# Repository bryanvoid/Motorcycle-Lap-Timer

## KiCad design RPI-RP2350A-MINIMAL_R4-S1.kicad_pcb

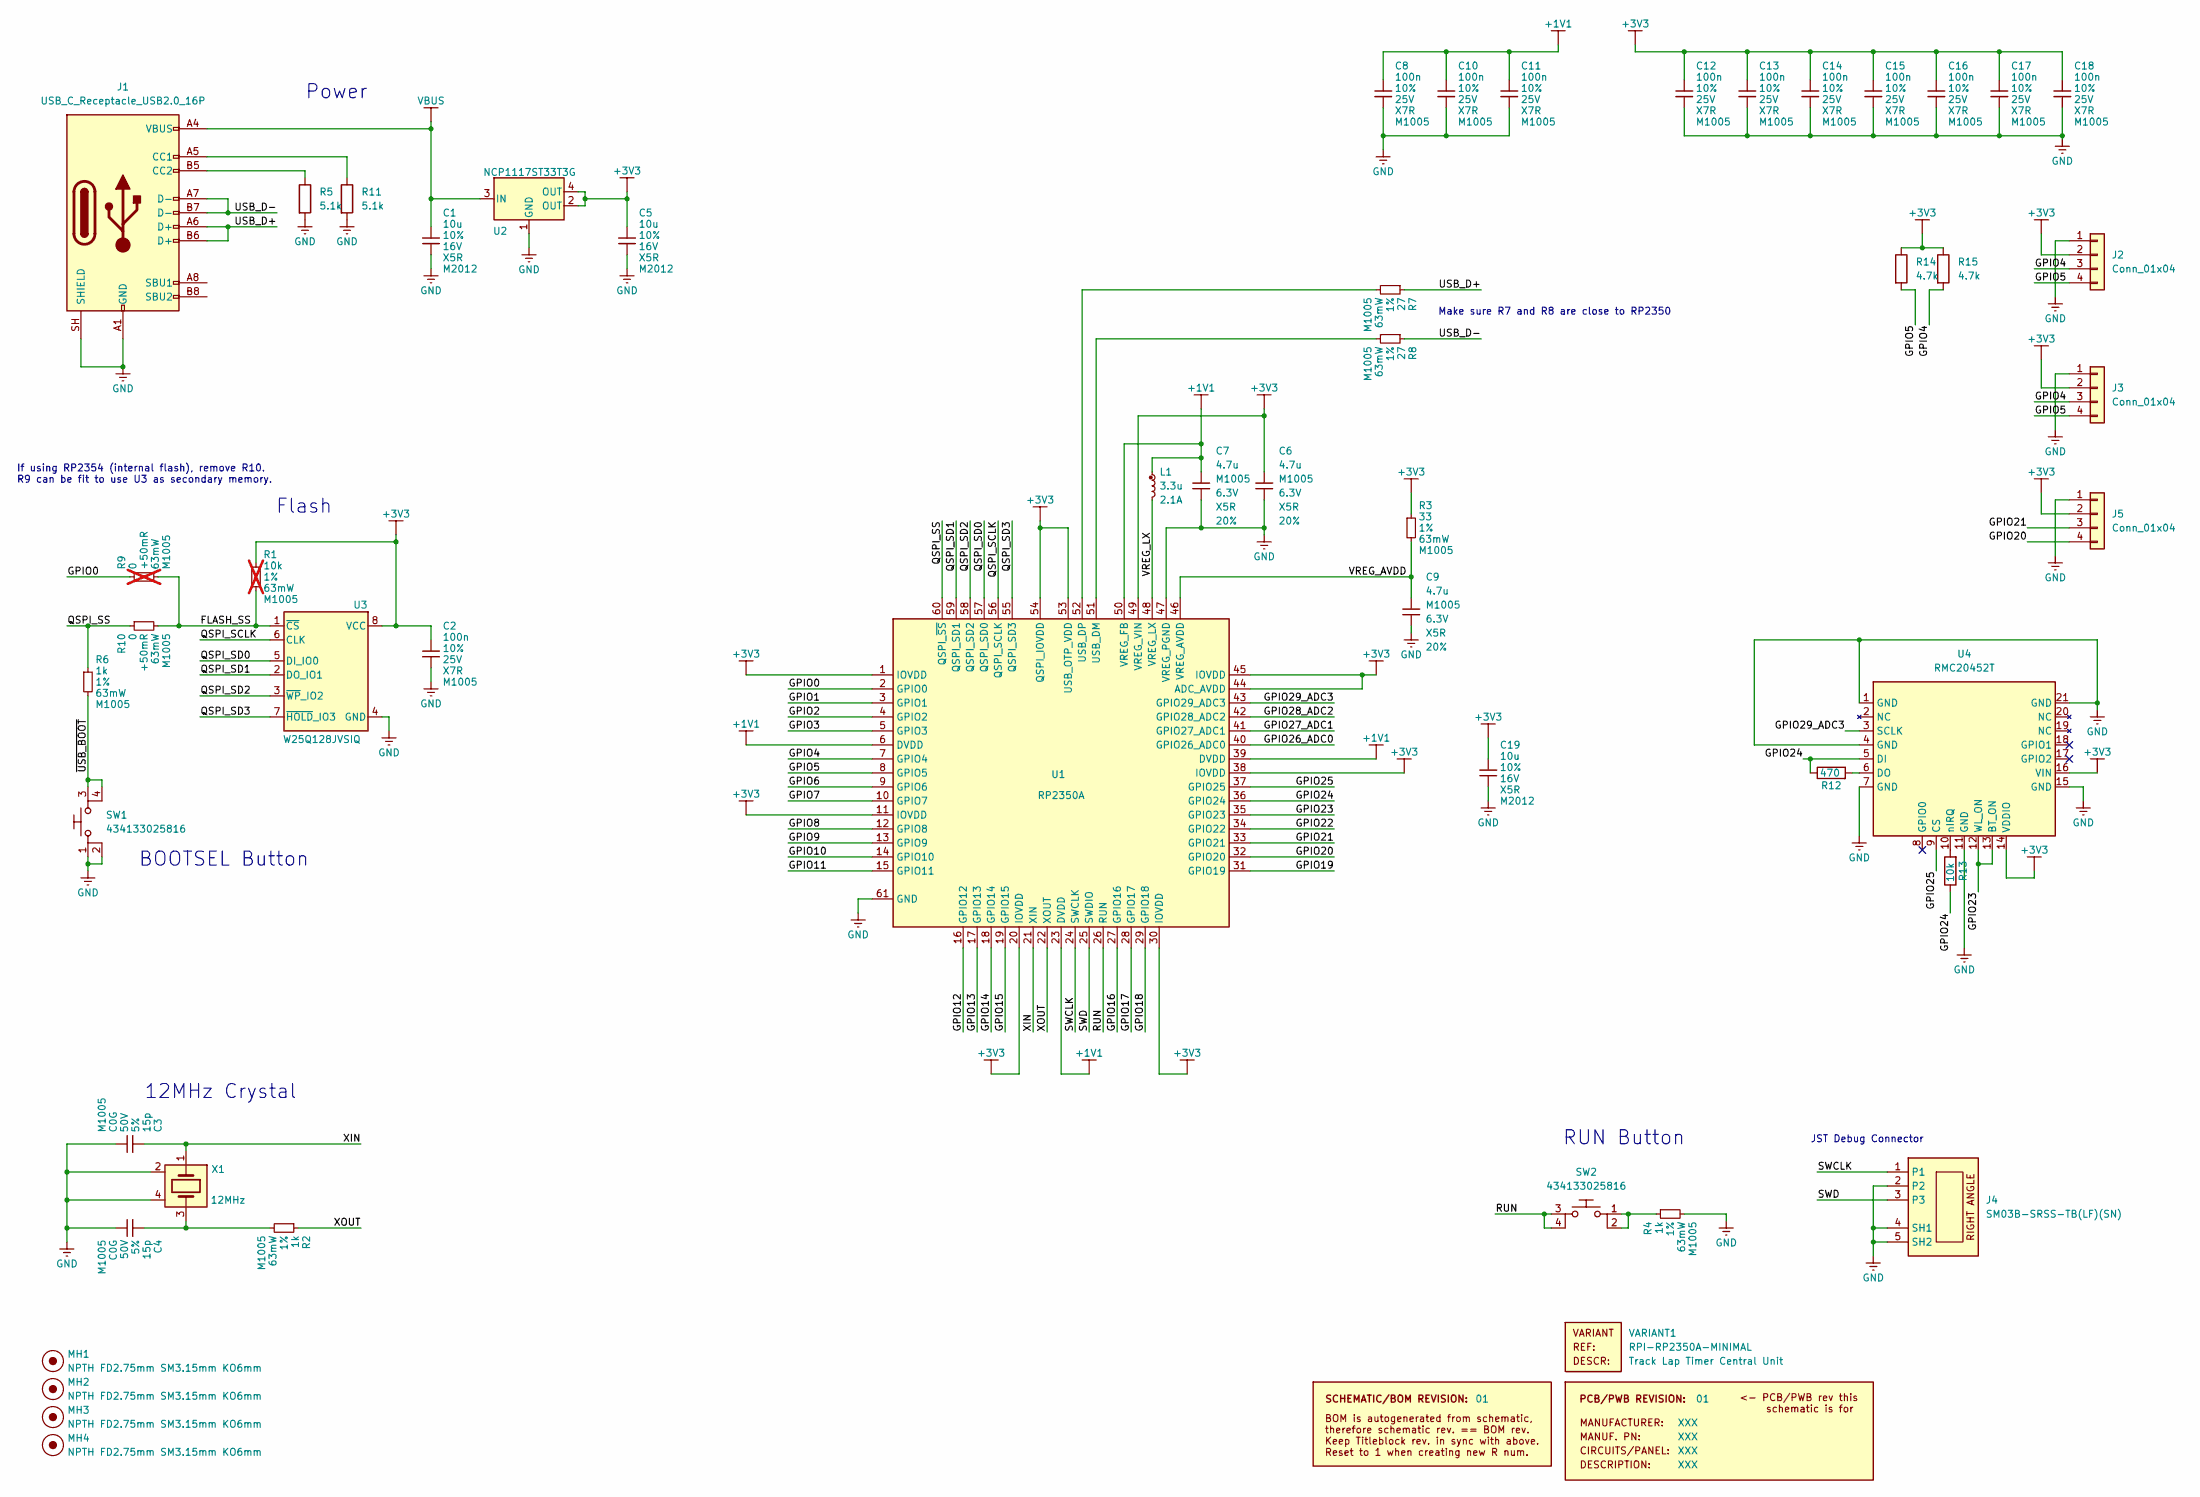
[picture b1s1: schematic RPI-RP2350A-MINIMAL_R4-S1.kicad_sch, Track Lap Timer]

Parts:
C1, C5, C19: 10u; generic_capc2012x125; voltage 16V; tolerance 10%; part_uid RP-01GYSK-AVBE41; LCSC C1035
C2, C8, C10, C11, C12, C13, C14, C15, C16, C17, C18: 100n; generic_capc1005x50; voltage 25V; tolerance 10%; part_uid RP-01BJ9Y-KRGF41; LCSC C1525
C3, C4: 15p; generic_capc1005x50; voltage 50V; tolerance 5%; part_uid RP-01C89W-LLY9XV; LCSC C1548
C6, C7: 4.7u; generic_capc1005x50_wide; voltage 6.3V; tolerance 20%; part_uid RP-019A1P-0C2GHY; LCSC C23733
C9: 4.7u; generic_capc1005x50; voltage 6.3V; tolerance 20%; part_uid RP-019A1P-0C2GHY; LCSC C23733
J1: USB_C_Receptacle_USB2.0_16P; USB_C_Receptacle_GCT_USB4110; LCSC C5143397
J2, J3, J5: Conn_01x04; JST_SH_SM04B-SRSS-TB_1x04-1MP_P1.00mm_Horizontal
J4: SM03B-SRSS-TB(LF)(SN); jst_sm03b-srss-tb-lf--sn-; part_uid RP-01EKJ1-8V9SV1; LCSC C160403
L1: 3.3u; L_Cenker_CKCS201610; tolerance 20%; part_uid RP-01GY5D-2VC7WP; LCSC C98035
MH1, MH2, MH3, MH4: NPTH FD2.75mm SM3.15mm KO6mm; none_mh_npth_fd2p75mm_sm3p15mm_ko6mm; part_uid RP-01HF5R-LCTEJS
PCB1: 01; manufacturer_pn XXX
R1: 10k; generic_resc1005x35; tolerance 1%; voltage 50V; part_uid RP-019A1P-53DHSX; LCSC C11616; not fitted
R2, R4, R6: 1k; generic_resc1005x35; tolerance 1%; voltage 50V; part_uid RP-019A1P-4Z6ZWY; LCSC C11702
R3: 33; generic_resc1005x35; tolerance 1%; voltage 50V; part_uid RP-019A1P-58PW9L; LCSC C25105
R5, R11: 5.1k; R_0402_1005Metric; LCSC C25905
R7, R8: 27; generic_resc1005x35; tolerance 1%; voltage 50V; part_uid RP-01C89V-LTEYC4; LCSC C25156
R9: 0; generic_resc1005x35; tolerance +50mR; voltage 50V; part_uid RP-019A1P-4Y4V63; LCSC C1002; not fitted
R10: 0; generic_resc1005x35; tolerance +50mR; voltage 50V; part_uid RP-019A1P-4Y4V63; LCSC C1002
R12: 470; R_0402_1005Metric; LCSC C25117
R13: 10k; R_0402_1005Metric; LCSC C25744
R14, R15: 4.7k; R_0402_1005Metric
SBREV1: 01
SW1, SW2: 434133025816; wurthelek_434133025816; part_uid RP-01H0MT-6E9H8F; LCSC C5504987
U1: RP2350A; rpi_rp2350a_vias; part_uid RP-01HA9H-9K5E8T; LCSC C42411118
U2: NCP1117ST33T3G; onsemi_ncp1117st33t3g; voltage 3.3V; part_uid RP-01JWD9-7JRX6J; LCSC C26537
U3: W25Q128JVSIQ; generic_soic127p790x195-8; voltage 2.7-3.6V; part_uid RP-01JWD4-F1H4N9; LCSC C97521
U4: RMC20452T; LCSC C49451547
VARIANT1: RPI-RP2350A-MINIMAL
X1: 12MHz; ABM8-272-T3_ABR; tolerance 30ppm; part_uid RP-01G8X7-GS352B; LCSC C9002

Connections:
+1V1: C7.1, C8.1, C10.1, C11.1, L1.1, U1.6 (DVDD), U1.23 (DVDD), U1.39 (DVDD), U1.50 (VREG_FB)
+3V3: C2.1, C5.1, C6.1, C12.1, C13.1, C14.1, C15.1, C16.1, C17.1, C18.1, C19.1, J2.2, J3.2, J5.2, R1.1, R3.1, R14.1, R15.1, U1.1 (IOVDD), U1.11 (IOVDD), U1.20 (IOVDD), U1.30 (IOVDD), U1.38 (IOVDD), U1.44 (ADC_AVDD), U1.45 (IOVDD), U1.49 (VREG_VIN), U1.53 (USB_OTP_VDD), U1.54 (QSPI_IOVDD), U2.2 (OUT), U2.4 (OUT), U3.8 (VCC), U4.14 (VDDIO), U4.16 (VIN)
/FLASH_SS: R1.2, R9.2, R10.2, U3.1 (~CS)
/GPIO0: R9.1, U1.2 (GPIO0)
/GPIO1: U1.3 (GPIO1)
/GPIO2: U1.4 (GPIO2)
/GPIO3: U1.5 (GPIO3)
/GPIO4: J2.3, J3.3, R15.2, U1.7 (GPIO4)
/GPIO5: J2.4, J3.4, R14.2, U1.8 (GPIO5)
/GPIO6: U1.9 (GPIO6)
/GPIO7: U1.10 (GPIO7)
/GPIO8: U1.12 (GPIO8)
/GPIO9: U1.13 (GPIO9)
/GPIO10: U1.14 (GPIO10)
/GPIO11: U1.15 (GPIO11)
/GPIO12: U1.16 (GPIO12)
/GPIO13: U1.17 (GPIO13)
/GPIO14: U1.18 (GPIO14)
/GPIO15: U1.19 (GPIO15)
/GPIO16: U1.27 (GPIO16)
/GPIO17: U1.28 (GPIO17)
/GPIO18: U1.29 (GPIO18)
/GPIO19: U1.31 (GPIO19)
/GPIO20: J5.4, U1.32 (GPIO20)
/GPIO21: J5.3, U1.33 (GPIO21)
/GPIO22: U1.34 (GPIO22)
/GPIO23: U1.35 (GPIO23), U4.12 (WL_ON), U4.13 (BT_ON)
/GPIO24: R12.1, R13.1, U1.36 (GPIO24), U4.5 (DI)
/GPIO25: U1.37 (GPIO25), U4.9 (CS)
/GPIO26_ADC0: U1.40 (GPIO26_ADC0)
/GPIO27_ADC1: U1.41 (GPIO27_ADC1)
/GPIO28_ADC2: U1.42 (GPIO28_ADC2)
/GPIO29_ADC3: U1.43 (GPIO29_ADC3), U4.3 (SCLK)
/QSPI_SCLK: U1.56 (QSPI_SCLK), U3.6 (CLK)
/QSPI_SD0: U1.57 (QSPI_SD0), U3.5 (DI_IO0)
/QSPI_SD1: U1.59 (QSPI_SD1), U3.2 (DO_IO1)
/QSPI_SD2: U1.58 (QSPI_SD2), U3.3 (~WP_IO2)
/QSPI_SD3: U1.55 (QSPI_SD3), U3.7 (~HOLD_IO3)
/QSPI_SS: R6.1, R10.1, U1.60 (QSPI_~SS)
/RUN: SW2.3, SW2.4, U1.26 (RUN)
/SWCLK: J4.1, U1.24 (SWCLK)
/SWD: J4.3, U1.25 (SWDIO)
/USB_D+: J1.A6 (D+), J1.B6 (D+), R7.1
/USB_D-: J1.A7 (D-), J1.B7 (D-), R8.1
/VREG_AVDD: C9.1, R3.2, U1.46 (VREG_AVDD)
/VREG_LX: L1.2, U1.48 (VREG_LX)
/XIN: C3.1, U1.21 (XIN), X1.1
/XOUT: R2.1, U1.22 (XOUT)
/~USB_BOOT: R6.2, SW1.3, SW1.4
GND: C1.2, C2.2, C3.2, C4.2, C5.2, C6.2, C7.2, C8.2, C9.2, C10.2, C11.2, C12.2, C13.2, C14.2, C15.2, C16.2, C17.2, C18.2, C19.2, J1.A1 (GND), J1.A12 (GND), J1.B1 (GND), J1.B12 (GND), J1.SH (SHIELD), J2.1, J3.1, J4.2, J4.4 (SH1), J4.5 (SH2), J5.1, R4.2, R5.2, R11.2, SW1.1, SW1.2, U1.47 (VREG_PGND), U1.61 (GND), U2.1 (GND), U3.4 (GND), U4.1 (GND), U4.4 (GND), U4.7 (GND), U4.11 (GND), U4.15 (GND), U4.21 (GND), X1.2, X1.4
unnamed: C4.1, R2.2, X1.3
unnamed: J1.A5 (CC1), R11.1
unnamed: J1.B5 (CC2), R5.1
unnamed: R4.1, SW2.1, SW2.2
unnamed: R8.2, U1.51 (USB_DM)
unnamed: R7.2, U1.52 (USB_DP)
unnamed: R12.2, U4.6 (DO)
unnamed: R13.2, U4.10 (nIRQ)
VBUS: C1.1, J1.A4 (VBUS), J1.A9 (VBUS), J1.B4 (VBUS), J1.B9 (VBUS), U2.3 (IN); also elsewhere on the board

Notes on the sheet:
JST Debug Connector
RUN Button
BOOTSEL Button
If using RP2354 (internal flash), remove R10. R9 can be fit to use U3 as secondary memory.
Flash
Make sure R7 and R8 are close to RP2350
12MHz Crystal
Power

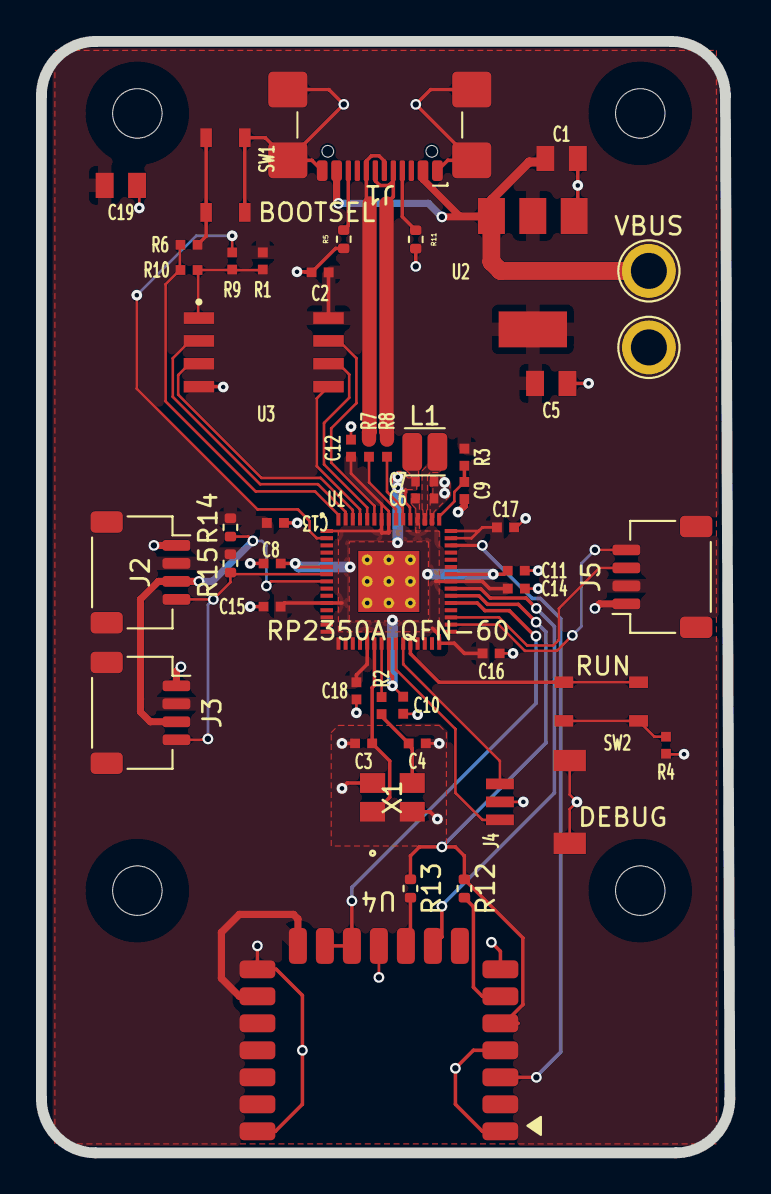
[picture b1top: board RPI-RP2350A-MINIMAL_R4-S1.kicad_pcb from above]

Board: 2 copper layers, 38.2 x 61.8 mm, 52 parts (0 on the bottom side), 38 nets.

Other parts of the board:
VBUS: TestPoint_Plated_Hole_D2.0mm

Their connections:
VBUS: VBUS.1; also elsewhere on the board

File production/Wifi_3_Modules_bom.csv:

Designator,Footprint,Quantity,Value,LCSC Part #
"C1, C19, C5",generic_capc2012x125,3,10u,C1035
"C10, C11, C12, C13, C14, C15, C16, C17, C18, C2, C8",generic_capc1005x50,11,100n,C1525
"C3, C4",generic_capc1005x50,2,15p,C1548
"C6, C7",generic_capc1005x50_wide,2,4.7u,C23733
C9,generic_capc1005x50,1,4.7u,C23733
J1,USB_C_Receptacle_GCT_USB4110,1,USB_C_Receptacle_USB2.0_16P,C5143397
"J2, J3, J5",JST_ACH_BM04B-ACHSS-A-GAN-ETF_1x04-1MP_P1.20mm_Vertical,3,Conn_01x04,
J4,jst_sm03b-srss-tb-lf--sn-,1,SM03B-SRSS-TB(LF)(SN),C160403
L1,L_Cenker_CKCS201610,1,3.3u,C98035
R10,generic_resc1005x35,1,0,C1002
"R11, R5",0402,2,5.1k,C25905
R12,0402,1,470,C25117
R13,0402,1,10k,C25744
"R14, R15",0402,2,4.7k,
"R2, R4, R6",generic_resc1005x35,3,1k,C11702
R3,generic_resc1005x35,1,33,C25105
"R7, R8",generic_resc1005x35,2,27,C25156
"SW1, SW2",wurthelek_434133025816,2,434133025816,C5504987
U1,rpi_rp2350a_vias,1,RP2350A,C42411118
U2,onsemi_ncp1117st33t3g,1,NCP1117ST33T3G,C26537
U3,generic_soic127p790x195-8,1,W25Q128JVSIQ,C97521
U4,RMC20452T,1,RMC20452T,C49451547
X1,ABM8-272-T3_ABR,1,12MHz,C9002
